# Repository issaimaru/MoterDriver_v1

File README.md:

# DriveUnit Bseries
**[自作電源基板](https://github.com/Issaimaru/PowerSupply_v1)に刺して使う80A級モータードライバ**<br>
**[DUB with 遠野](https://github.com/Issaimaru/DUB_with_Tono)を使って遠野に刺すこともできます**<br>
**動作電圧 8[V]~30[V]**<br>
**PWM周波数 ~250kHz**<br>
**duty比 100%対応**<br>
**電圧監視機能搭載**<br>
**LAP/SM方式での駆動が可能**<br>
**制作期間:2022/01/18頃～**<br>
**名前:DriveUnit Bseries**<br>

## バージョンに対応するドキュメント
- ver1.0-->[README_v1.md](https://github.com/Issaimaru/MoterDriver_v1/blob/master/README_v1.md)
- ver2.0-->[README_v2.md](https://github.com/Issaimaru/MoterDriver_v1/blob/master/README_v2.md)

## 前モータードライバ(野獣)との違い
野獣がノートパソコンで，DUBがゲーミングパソコンと例えるとわかりやすいと思います．(やや過言かもしれないです...)<br>
野獣ができることは基本的にDUBでもできますし，野獣でできないような機能もDUBにはありますが，値段とサイズ的にはDUBが劣ります．<br>
- **PWM比1.0での動作が可能**<br>
このモータードライバで使用しているA3921というゲートドライバは，ハイサイドにチャージポンプを内蔵しています．そのため，PWM比が1.0の近くであっても正常に動作することができます．<br>

- **動作周波数帯域が増えた**<br>
    > 100Hz以上10000Hz未満なら一応動く。一番特性がいいのは2kHz。<br>
 
  富山本郷メカテック部wikiの野獣の説明にはこのように書いてありますが，20kHzまでは人間の可聴域なので20kHz以下でモータを駆動させると大きな音がモータから発せられてしまいます．      <br>DriveUnit Bseries(以下，DUBといいます．)は ~~**計算上では**100kHzでも動作します．これは実験で確かめます．~~　<br>
  実験したところ，mbedではPWM周波数に比例してPWM分解能が小さくなるため，20kHzを超えると明らかにモーターの動作が不安定になります．
  <br>STM32CubeIDEからHALドライバーを使用し，タイマーの設定を変更することでこの問題を解消することができますが([ここ](https://qiita.com/ShunHattori/items/68f099f1d77702d2535d)を参照)，普通はオンラインコンパイラから制御しますよね...(実際にHALドライバーを使用してやってみましたが色々めんどくさいです)<br>
  上記の問題から，HALドライバーを使用せずにこのモータードライバを使用する場合は10kHz~20kHzで使用することを推奨します．(可聴域内ですが，音は聞こえないです．)<br>
  また，HALドライバーを使用する場合は250kHz以下の周波数で使用するようにしてください．
  
- **LAP/SM方式の切り替えが可能**<br>
このモータードライバで使用しているA3921というゲートドライバの配線をうまくしてやると，PWM方式(LAP/SM)をスイッチ一つで切り替えることが実現できます．SM方式はPWM比がそのまま回転数と比例し，効率がよく，低周波でも線形性が比較的保たれるのに対して，LAP方式は正転と逆転の比率を調整してモータの回転方向と回転速度を変化させる方式であり，Duty比50%でモーターが停止するという違いがあります．

- **定格電圧が大きくなった**<br>
モータードライバでは逆起電力が生じるため加える電圧の2倍程度のマージンを取る必要がある(と他高専のOBの方からアドバイスを頂きました．)<br>そのため， $V_{DS}$ が30 $V$ のFETを使用し，コンデンサやゲートドライバの耐圧も30 $V$ 以上になるように選定しました．<br>また，パスコンには(これも他高専のOBの方のアドバイスで)高分子コンデンサを使用しました．<br>そのため，野獣よりも逆起電力に強くなりましたが，6セルのリポバッテリー等を使って急減速をすると逆起電力で普通に30 $V$ を超えます(上の「特性」を参照)．そのため，6セルのリポバッテリー等を使用する場合は電源ラインをオシロスコープで確認して，逆起電力で30 $V$ を超えないか確認することを推奨します．

- **ボタンでモータを制御できるようになった**<br>
MD10Cのように，ボタンでモータの正転，逆転を制御できるようにしました．

- **定格電流が大きくなった**<br>
DUBでは(これも実験で確かめますが)最大で連続80 $A$ の電流を流すことができます．しかし，ハピロボ以降のロボコンは30 $A$ 以下という電流制限があるため，電源基板側にリセッタブルヒューズがついています．そのためあまり意味はありません．<br>

- **電圧監視機能が付いた**<br>
これもA3921の機能ですが，ハイサイドのFETの $V_{DS}$ 間の電圧を監視することによって万が一短絡した場合でもすぐに動作を止めてくれるほか，オーバーヒートしてるような状態なども検知してFFXのLEDを光らせることで警告してくれます．<br>
A3921のデータシートから取ってきたものですが，各FFピンの出力に対する説明は以下の表の通りとなっています．<br>

- **逆接しにくくなった**<br>
エッジコネクタは物理的に逆接が不可能な状態になっていませんが，野獣は勿論のことこのモータードライバも逆接すると燃えます．<br>
そのため，このモータードライバと電源基板では三角の印をつけることで接続する向きが把握しやすいようにしました．<br>

## はんだ付けの仕方
長くなるのでたたみます．
<details><summary>はんだ付けの仕方</summary>
まず初めに，このモータードライバのはんだ付けはとてもめんどくさいです．<br>
なぜなら，はんだごてではんだ付けするにはあまりにも小さすぎる部品を使っているため，リフローをする必要があるからです(恐らく部内でリフローする基板はこれが初めて)．<br>
といっても，部内にはリフローオーブンなんてないので....<br>

<br>
ホットプレートを使用したホットプレートリフローではんだ付けしています．<br>
ていっても，基板は両面ありますが片面をホットプレートリフローしてもう片面も同じようにやろうとすると，はんだ付け済みの面が先に温まってしまうので両面をこの方法ですることはできません．そこでもう片面は.......<br>

ヒートガンを使用したヒートガンリフローではんだ付けしています．<br>
そのため，~~本当にめんどくさい~~ですが一気にはんだ付けできるため手はんだとどっちがめんどくさいかと聞かれるとどっちもどっちかなと思います．<br>
とりあえず，はんだづけの仕方を書いておかないと正直量産は自分以外に難しくなってしまうのでここに書いておきます．<br>

まず，ホットプレートリフローをする面は裏面(下の画像で示している面)です．<br>
<br>

理由は，この基板ではんだ付けが一番難しい部品がこの面のICで，こっちの面をヒートガンでリフローするとリフローの風ではんだが飛んで隣同士がくっついてしまう可能性があるからです．<br>
ホットプレートリフローについては[ここ](https://qiita.com/azusa9/items/a2fc4f26799de5588c58)を見ればやり方は完全理解することができると思いますが，一応自分流のやり方を書いておきます．<br>

1. いらない基板を3つ用意してDUBを囲うように配置する．
    <br>
    画像のように，DUBより大きめの基板をDUBの周りに配置します．<br>

1. テープ(できれば養生)で固定する．
    <br>
    こんな感じでDUBが動かないように固定してください．あとから剥がすので養生の方がいいです．自分は家に養生テープがなかったのでセロハンテープでやってます．

1. ステンシル(メタルマスク)をパッドに合わせて上だけテープで固定する
    <br>
    ステンシルの穴がパッドにしっかりと合うようにして，上だけをテープで固定します．<br>
    上だけを固定する理由は後で説明します．

1. クリーム半田をいらないカード等で伸ばしながら塗る<br>
    
    <br>
    部室に画像のようなクリームはんだがあると思います．(なければ買ってください．自分は[ここ](https://www.amazon.co.jp/gp/product/B09QCQ12RV/ref=ppx_yo_dt_b_asin_title_o00_s00?ie=UTF8&psc=1)で買いました．)<br>
    これをまずはステンシルに落として，いらないカードなどで伸ばして基板のパッド全てに塗られるようにしてください．<br>
    自分は部室にこれを忘れてきたので塗りませんが，こんな感じです([超簡単、ホットプレートでリフロー（はんだ付け）！](https://qiita.com/azusa9/items/a2fc4f26799de5588c58#%E3%81%84%E3%81%96%E3%82%AF%E3%83%AA%E3%83%BC%E3%83%A0%E5%8D%8A%E7%94%B0%E5%A1%97%E3%82%8A)より引用)．<br>

    <br>

1. ステンシルの上に貼ったテープを支点にステンシルを持ち上げ，部品を乗せる．<br>
    ステンシルの固定の際に上だけをテープで固定した理由はこれを支点にステンシルを持ち上げるからです．<br>
    塗ったクリームはんだを壊さないようにゆっくりと持ち上げたら，いよいよ部品をピンセットで載せていきます．<br>
    ここで注意点をまとめておきます．<br>
    
    - 部品を乗せる際，きっちり押さえつける必要はない．
    - リフローの際に自然にパターンの位置に部品が動くため，多少部品がずれていても修正しない．
    - 特にIC部ははんだが隣同士でくっつくが，修正せずにICを載せる．
    
    以上の注意点を頭に入れながら，部品を載せていきます．<br>
    ちなみに載せるのは表面実装部品のみで，スルーホール部品はまだはんだ付けしません．<br>
    いちいち回路図を参照しながら部品を載せるのはめんどくさいと思うのでここに載せる部品をまとめておきます．(これはver1.0の部品配置です．ver1.0以降のバージョンの部品配置は各ドキュメントに示しておきます．)<br>
    <br>
    この画像の通りに部品を配置したら，いよいよホットプレートリフローに入ります．<br>

1. ホットプレートリフロー!<br>
    ホットプレートの中心に部品を載せた基板を置き，ホットプレートを加熱していきましょう．部室にあるホットプレートなら中~強の間に合わせればいいと思います．<br>
    そのまま待っていると，煙がでてきてクリームはんだが溶け，金属光沢が現れると思います．全体的にクリームはんだがこの状態になったらホットプレートの加熱をやめ，動かさずに冷えるまで待ってください．<br>
    冷えてはんだが固まったら裏面については終わりです．お疲れ様でした．最後に導通試験をしてください(特にIC)．<br>
    <br>
    **ICの隣同士がくっついていた場合**<br>
    これはよくあります．こうなった場合は，ハンダ吸い取り線で吸い取ってやるとうまく離れると思います．試してみてください．

1. 表面もはんだペーストを塗って部品を配置する<br>
    手順1~5と同様にして表面についてもはんだペーストを塗って，部品を載せます．<br>
    載せる部品をここにまとめておきます．<br>
    ここで，タクトスイッチの裏に丸い突起があるためそのまま置くとパッド面と密着しないと思います．<br>
    そのため突起をニッパー等で取ってから置くようにしてください．<br>

1. ヒートガンリフロー!<br>
    ヒートガンの風を直にあてて基板を加熱していきます．<br>
    設定は弱風にして，チップLEDの真上にヒートガンがあるようにしてください(チップLEDがヒートガンの風で吹き飛ばされる可能性があるため)．<br>
    このとき，机がヒートガンの熱で壊れる可能性があるので，可能であれば作業マットの上に基板をおいて作業をしましょう．<br>
    この状態でしばらくすると，チップLEDの周りの部品だけはんだが溶けてくると思います．<br>
    はんだが完全に溶けたら，ヒートガンを下にもっていって，タクトスイッチ等についても同様にリフローを行ってください．<br>
    全てのはんだペーストが溶けたら加熱をやめ，動かさずに冷えるまで待ってください．<br>
    冷えてはんだが固まったら表面実装部品のはんだ付けは終わりです．お疲れ様でした．<br>
    <br>
    **タクトスイッチがパッド面と密着せず，リフローに失敗した場合**<br>
    この場合は手はんだではんだ付けしてください．<br>

1. スルーホール部品を手はんだではんだ付けする<br>
    ここまで来たら楽です．あとはいつも通りスルーホール部品をはんだ付けしてください．<br>
    注意点をまとめておきます．<br>
    
    - FETのドレインのピン(3ピンあるうちの真ん中のピン)はニッパーで切る
    - 電解コンデンサは，基板が白で塗りつぶされている方がマイナス(紫色の印がある方)になるように付ける

1. 完成!<br>
    お疲れ様でした．最後に動作試験をしてみてちゃんと動いたらはんだ付けが正しくできています．    

</details>

## 回路図のダウンロード(クローン)方法
1. Gitをインストールします．<br>Gitのインストール方法は[ここ](https://www.sejuku.net/blog/73444)を参照してください．
1. コマンドプロンプトを立ち上げます．
1. `cd ”ダウンロード先フォルダの絶対パス” `<br>
1. `git clone https://github.com/Issaimaru/MoterDriver_v1.git`<br>

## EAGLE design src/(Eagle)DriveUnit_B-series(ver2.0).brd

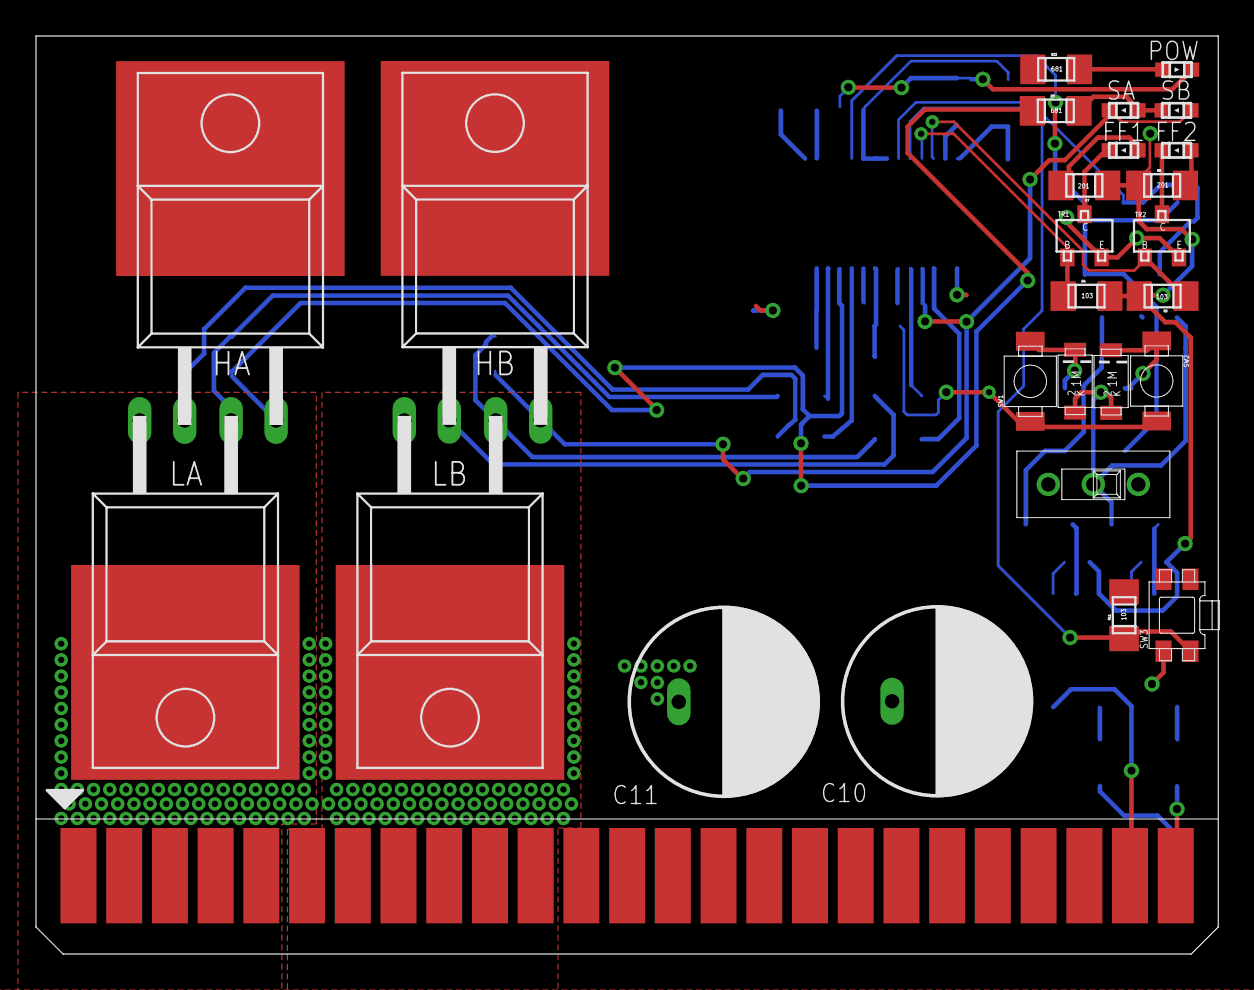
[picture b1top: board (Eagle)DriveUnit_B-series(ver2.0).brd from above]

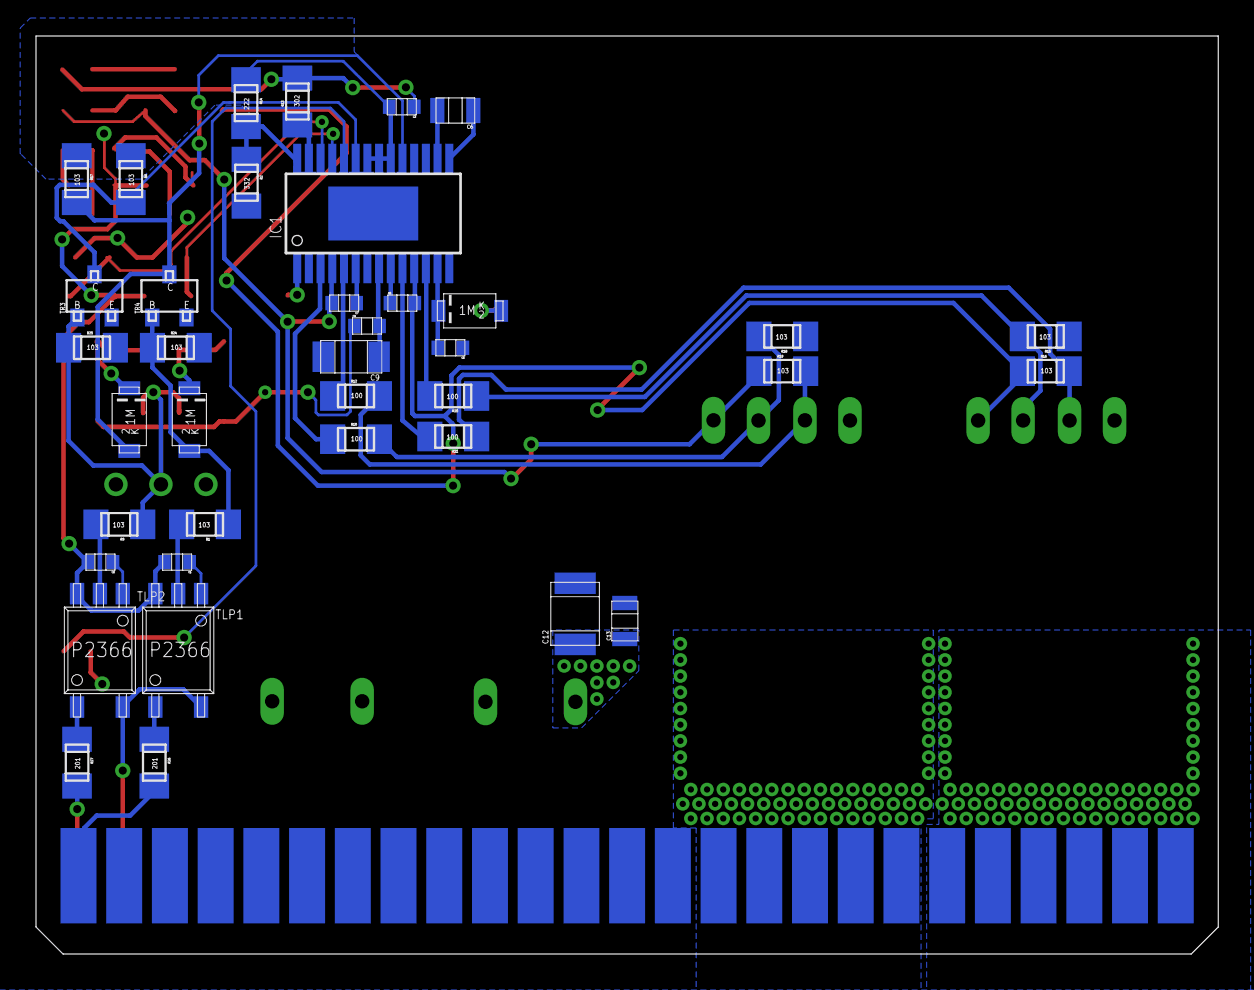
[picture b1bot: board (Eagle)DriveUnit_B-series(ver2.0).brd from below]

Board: 2 copper layers, 65.7 x 51.0 mm, 65 parts (38 on the bottom side), 43 nets.

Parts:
C1, C2, C3, C4, C5, C7, C8: GCM188L81H104KA57
C6: GCM21BR71H474KA55
C9: GRT31CC81H225KE01L
C10, C11: 35PZJ330M10X9
C12: GRM32ER7YA106KA12
C13: GRM21BC72A105KE01
D1, D2, D3, D4, D5: GS1010FL
EDGE1: 10046971-019LF
HA: IRLB3813NOHOLE; TO-220AB-NOHOLE
HB: IRLB3813NOHOLE; TO-220AB-NOHOLE
IC1: A3921
LA: IRLB3813NOHOLE; TO-220AB-NOHOLE
LB: IRLB3813NOHOLE; TO-220AB-NOHOLE
LED1, LED2, LED3, LED4, LED5: SML-E12V8WT86
R1, R4, R5, R6, R9, R11, R15, R16, R17, R18, R19, R24, R25: RG2012
R2: RG2012N-332-W-T1; RG2012
R3, R22: RG2012P-681-B-T5; RG2012
R7, R8, R26, R27: RG2012N-201-W-T1; RG2012
R10, R12, R20, R21: RG2012Q-100-D-T5; RG2012
R13: RG2012P-302-B-T5; RG2012
R14: RG2012N-222-W-T1; RG2012
SW1, SW2: TVAF06-A020B-R
SW3: THAF01-NC-R
SW4: SS-12D00G3
TLP1, TLP2: TLP2366
TR1, TR2, TR3, TR4: 2SC3325

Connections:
DIR: D3.A, IC1.19, R17.RIGHT, TR4.C
DIR_IN: EDGE1.P$26, R26.RIGHT
FF1: IC1.25, R4.LEFT, TR1.B
FF2: IC1.26, R5.LEFT, TR2.B
GHA: IC1.10, R21.RIGHT
GHB: IC1.5, R12.LEFT
GLA: IC1.12, R20.RIGHT
GLB: IC1.3, R10.LEFT
GND: C1.P$1, C2.P$1, C3.P$1, C4.P$1, C5.P$1, C9.P$2, C10.C, C11.C, C12.P$2, C13.P$2, EDGE1.P$28, EDGE1.P$29, EDGE1.P$30, EDGE1.P$31, EDGE1.P$32, EDGE1.P$33, EDGE1.P$34, EDGE1.P$35, EDGE1.P$36, EDGE1.P$37, EDGE1.P$38, EDGE1.P$39, IC1.2, IC1.17, IC1.PAD, LA.SOURCE, LB.SOURCE, LED3.K, R2.RIGHT, R13.RIGHT, R15.LEFT, R18.LEFT, R24.RIGHT, R25.RIGHT, SW1.LEFT, SW2.RIGHT, SW3.1, SW4.R, TLP1.4, TLP2.4, TR1.E, TR2.E, TR3.E, TR4.E
GND_IN: EDGE1.P$24, TLP1.3, TLP2.3
LAP: D4.A, D5.A, R9.LEFT, R25.LEFT, SW4.C, TR3.B
unnamed: C6.P$1, IC1.15
unnamed: C6.P$2, IC1.16
unnamed: C7.P$1, IC1.6
unnamed: IC1.28, R2.LEFT, R14.RIGHT
unnamed: LED4.K, TR1.C
unnamed: C4.P$2, C9.P$1, IC1.8
unnamed: C5.P$2, D1.C, IC1.13
unnamed: LED5.K, TR2.C
unnamed: LED4.A, R7.RIGHT
unnamed: LED5.A, R8.RIGHT
unnamed: R1.RIGHT, TLP1.5
unnamed: D2.C, D4.C, SW1.RIGHT
unnamed: HA.GATE, R16.RIGHT, R21.LEFT
unnamed: R9.RIGHT, TLP2.5
unnamed: C8.P$1, IC1.9
unnamed: D2.A, R1.LEFT, R24.LEFT, TR4.B
unnamed: LED1.A, LED2.K, R3.RIGHT
unnamed: IC1.27, R13.LEFT
unnamed: D3.C, D5.C, SW2.LEFT
unnamed: HB.GATE, R12.RIGHT, R19.RIGHT
unnamed: LED3.A, R22.RIGHT
unnamed: R26.LEFT, TLP1.1
unnamed: R27.LEFT, TLP2.1
unnamed: LA.GATE, R15.RIGHT, R20.LEFT
unnamed: LB.GATE, R10.RIGHT, R18.RIGHT
PWM: IC1.23, R6.RIGHT, TR3.C
PWM_IN: EDGE1.P$25, R27.RIGHT
RESET: IC1.24, R11.LEFT, SW3.3
SA: C8.P$2, EDGE1.P$1, EDGE1.P$2, EDGE1.P$3, EDGE1.P$4, EDGE1.P$5, EDGE1.P$45, EDGE1.P$46, EDGE1.P$47, EDGE1.P$48, EDGE1.P$49, EDGE1.P$50, HA.SOURCE, IC1.11, LA.DRAIN, R3.LEFT, R16.LEFT
SB: C7.P$2, EDGE1.P$6, EDGE1.P$7, EDGE1.P$8, EDGE1.P$9, EDGE1.P$10, EDGE1.P$11, EDGE1.P$40, EDGE1.P$41, EDGE1.P$42, EDGE1.P$43, EDGE1.P$44, HB.SOURCE, IC1.4, LB.DRAIN, LED1.K, LED2.A, R19.LEFT
V5: C1.P$2, C2.P$2, C3.P$2, IC1.20, IC1.21, IC1.22, R4.RIGHT, R5.RIGHT, R6.LEFT, R7.LEFT, R8.LEFT, R14.LEFT, R17.LEFT, TLP1.6, TLP2.6
VCC: C10.A, C11.A, C12.P$1, C13.P$1, D1.A, EDGE1.P$12, EDGE1.P$13, EDGE1.P$14, EDGE1.P$15, EDGE1.P$16, EDGE1.P$17, EDGE1.P$18, EDGE1.P$19, EDGE1.P$20, EDGE1.P$21, EDGE1.P$22, EDGE1.P$23, HA.DRAIN, HB.DRAIN, IC1.1, R11.RIGHT, R22.LEFT

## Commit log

2022-05-14 Create LICENSE
2022-05-15 brd編集 配線
2022-05-17 部品配置訂正 大電流パターン考慮
2022-05-17 edit:配線の追加
2022-05-18 edit:GND,VCCベタ,wireの追加
2022-05-19 edit:大体配線完了
2022-05-23 ビアの配置
2022-05-25 ビア,パターンの追加 ほぼ完成
2022-05-29 GNDパターンの強化
2022-06-15 配線の追加,整理
2022-06-16 配線を太くした
2022-06-17 配線完了
2022-06-17 KiCadへの移行,PCBデザインの完成
2022-06-18 配線の修正等
2022-06-18 DRCエラーの対処
2022-06-23 基板デザインの完成
2022-06-24 Update README.md
    部品のリストを更新
2022-06-24 Update README.md
    使用電子部品，及びその値段の表の追加
2022-06-24 Update README.md
    総額の追加
2022-06-24 Update README.md
    前モタドラとの違いを記述
2022-06-25 Update README.md
    回路図の追加
2022-06-25 gerberの出力,名前の変更
2022-06-25 fp-info-cacheの更新
2022-06-26 名前の変更
2022-06-28 Update README.md
    回路図のクローン方法の追加
2022-06-30 Eagle_ERCエラーの修復
2022-06-30 Update README.md
    説明の追加
2022-06-30 Update README.md
    linkの更新
2022-07-01 意図的なconflict
2022-07-01 conflict前段階
2022-07-01 意図conflict new側
2022-07-01 conflict old側
2022-07-01 背面パッドの考慮
2022-07-01 conflict解消 サーマルパッドの考慮
2022-07-01 gerberの更新
2022-07-01 Update .gitignore
    Eagleの追加
2022-07-02 GNDベタの修正
2022-07-02 ガバ設計による炎上回避(GNDベタを大きくした)
2022-07-02 シルクの修正
2022-07-02 Update README.md
    FFXピンの説明
2022-07-03 FF2の配線の修正
2022-07-05 フォトカプラLED入力に200ohm抵抗付けた
2022-07-05 Update README.md
    表の画像の修正
2022-07-06 Update README.md
    R4，R17の追加
2022-07-09 Update README.md
    ページの追加，敬語
2022-07-11 Update README.md
    機能の説明の追加
2022-08-04 説明の追加
2022-08-05 readme.mdの編集
2022-08-05 折りたたみの追加
2022-08-06 readme.mdに不具合の追加
2022-08-06 Update README.md
    ミスの修正
2022-08-06 Update LICENSE
2022-08-08 Update README.md
    修正点の追加
2022-08-11 はんだ付けの仕方の説明の追加
2022-08-12 read.me更新
2022-08-12 readme.mdの更新
2022-08-14 ヒートガンリフローの説明の追加
2022-08-14 はんだ付けの説明終了
2022-08-30 [fix]入力周りなどの変更(ver1.0の問題点の修復)
2022-09-01 入力部分の追加
2022-09-01 README_v1等の追加
2022-09-01 回路図の偏向
2022-09-02 [fix]デッドタイムを100kΩ可変抵抗で調整できるように変更
2022-09-02 [add]電流センサ周りの配線_1
2022-09-15 [remove:電流センサを取り除いた
2022-09-15 [add]配線の追加
2022-09-16 入力部の配線の追加
2022-09-16 [add]部品配置完了
2022-09-16 [add]9/16進捗分
2022-09-18 配線の追加
2022-09-19 ビアなどの追加
2022-09-19 SA，SBベタ以外は配線終了．
2022-09-20 配線の終了
2022-09-20 モタドラ配線完全終了_KiCad移行前
2022-09-20 kicad完全移行_シルク配置全完
2022-09-20 デザイン完了
2022-09-21 ver2.0完全完了_gerber出力前
2022-09-21 ver2.0ちょい修正_gerber出力前
2022-09-21 gerber出力完了
2022-09-22 回路ミスってた(嘘だろ...)_KiCad以降前
2022-09-22 修正前ファイルを消した_KiCad以降前
2022-09-22 KiCad移行後_schファイル破壊
2022-09-22 KiCad移行後_破壊ファイルの修正
2022-09-22 表デザイン完成
2022-09-22 デザイン途中まで
2022-09-23 基板デザインの完全完成_gerber出力前
2022-09-23 gerber出力後
2022-09-23 gerber出力 一応もう一回(え？)
2022-09-24 readmeの更新
2022-09-27 markdownの更新
2022-09-28 markdown_v2の更新3
